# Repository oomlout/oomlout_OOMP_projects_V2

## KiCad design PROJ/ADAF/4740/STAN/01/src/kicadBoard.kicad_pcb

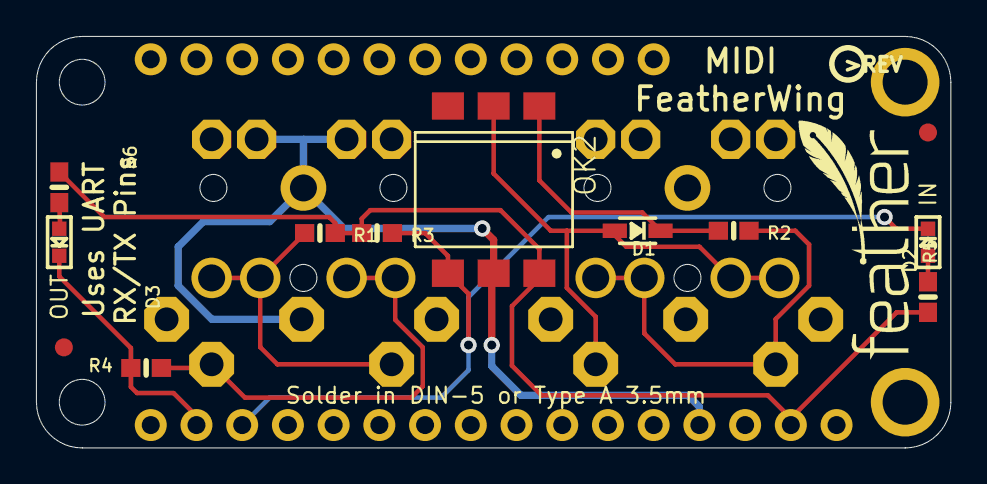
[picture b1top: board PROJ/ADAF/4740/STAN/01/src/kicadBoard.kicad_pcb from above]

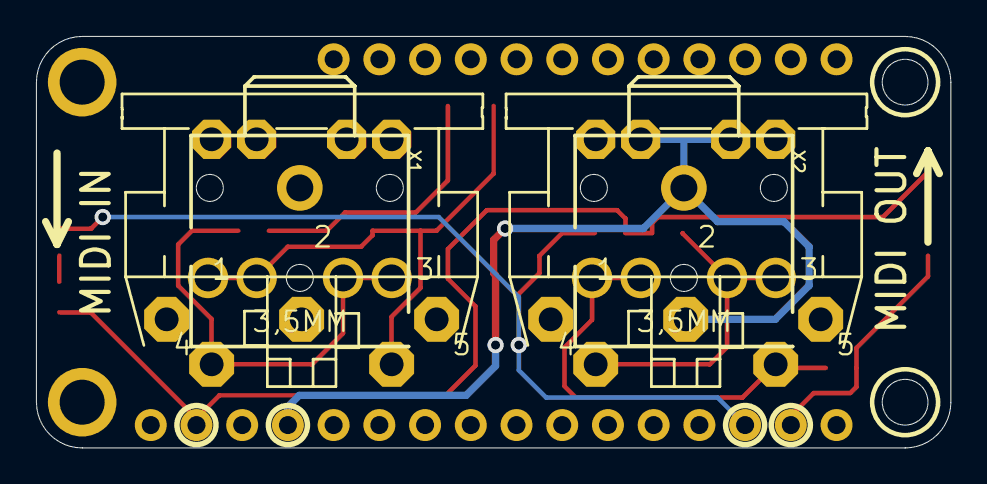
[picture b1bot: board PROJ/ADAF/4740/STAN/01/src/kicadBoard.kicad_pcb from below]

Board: 2 copper layers, 50.8 x 22.9 mm, 19 parts (5 on the bottom side), 11 nets.

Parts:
D1: 1N4148; SOD-323
D2, D3: BLUE; CHIPLED_0603
FID1, FID2: FIDUCIAL_1MM
MIDIIN0: DIN_5; CP-2350
MIDIOUT0: DIN_5; CP-2350
MS1: FEATHERWING_NODIM
OK2: H11L1MS; DIL6-SMD
R1: 33; 0603-NO
R2: 220; 0603-NO
R3: 470; 0603-NO
R4: 10; 0603-NO
R5, R6: 2.2K; 0603-NO
U$8: PCBFEAT-REV-040
U$9: FEATHERLOGO_SMALL
X1, X2: 3.5mm; STX3100

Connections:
3.3V: MS1.2, OK2.6, R1.2, R3.1, R5.1, R6.1
GND: MIDIOUT0.2, MIDIOUT0.PE, MIDIOUT0.PE@, MS1.4, OK2.5, X2.1
IN_SINK: D1.A, MIDIIN0.5, OK2.2, X1.4, X1.5
IN_SOURCE: MIDIIN0.4, R2.2, X1.2, X1.3
MIDI_RX: D2.C, MS1.14, OK2.4, R3.2
MIDI_TX: D3.C, MS1.15, R4.2
unnamed: D2.A, R5.2
unnamed: D3.A, R6.2
unnamed: D1.C, OK2.1, R2.1
OUT_SINK: MIDIOUT0.5, R4.1, X2.4, X2.5
OUT_SOURCE: MIDIOUT0.4, R1.1, X2.2, X2.3

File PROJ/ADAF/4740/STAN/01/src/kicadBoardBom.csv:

"Id";"Designator";"Package";"Quantity";"Designation";"Supplier and ref";
1;"U$8";"PCBFEAT-REV-040";1;"";;;
2;"R6,R5";"0603-NO";2;"2.2K";;;
3;"D1";"SOD-323";1;"1N4148";;;
4;"R2";"0603-NO";1;"220";;;
5;"D2,D3";"CHIPLED_0603";2;"BLUE";;;
6;"FID1,FID2";"FIDUCIAL_1MM";2;"FIDUCIAL_1MM";;;
7;"R4";"0603-NO";1;"10";;;
8;"R3";"0603-NO";1;"470";;;
9;"U$9";"FEATHERLOGO_SMALL";1;"";;;
10;"OK2";"DIL6-SMD";1;"H11L1MS";;;
11;"R1";"0603-NO";1;"33";;;
12;"MS1";"FEATHERWING_NODIM";1;"FEATHERWING_NODIM";;;
13;"X1,X2";"STX3100";2;"3.5mm";;;
14;"MIDIOUT0,MIDIIN0";"CP-2350";2;"DIN_5";;;

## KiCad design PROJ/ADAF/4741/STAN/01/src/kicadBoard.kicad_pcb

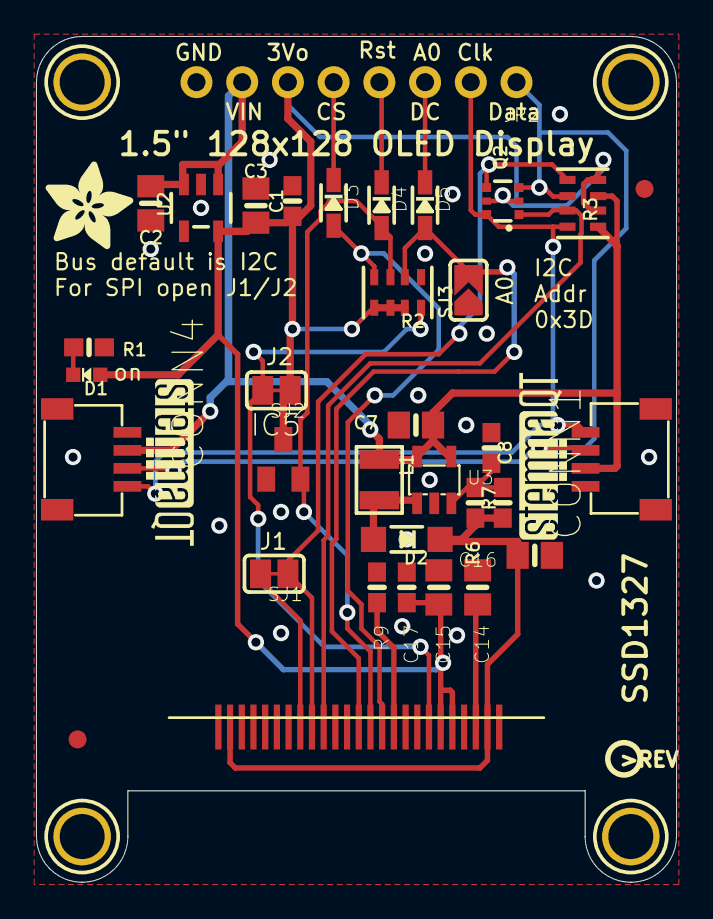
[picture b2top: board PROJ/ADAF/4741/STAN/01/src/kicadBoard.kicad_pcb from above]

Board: 2 copper layers, 35.6 x 47.0 mm, 42 parts (1 on the bottom side), 21 nets.

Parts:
C1, C8: 0.1uF; 0603-NO
C2, C3, C7, C14, C15, C16: 10uF; 0805-NO
C17: 1uF; 0603-NO
CONN1, CONN4: STEMMA_I2C_QT; JST_SH4
D1: GREEN; CHIPLED_0603_NOOUTLINE
D2: MBR120; SOD-123
D3, D4, D5: 1N4148; SOD-323
FID3, FID4: FIDUCIAL_1MM
IC5: APX803; SOT23
JP2: 1X08_ROUND_70
L1: 10uH; INDUCTOR_1007
Q2: BSS138; SOT363
R1, R7: 10K; 0603-NO
R2, R3: 10K; RESPACK_4X0603
R6: 100K; 0603-NO
R9: 390K; 0603-NO
SJ1, SJ2: SOLDERJUMPER_CLOSEDWIRE
SJ3: SOLDERJUMPER_ARROW_NOPASTE
U2: AP2112K-3.3; SOT23-5
U3: FAN5331SX; SOT23-5@1
U$1, U$17, U$19, U$21: MOUNTINGHOLE2.5; MOUNTINGHOLE_2.5_PLATED
U$8: ADAFRUIT_5MM
U$20, U$31: STEMMAQT
U$25: PCBFEAT-REV-040
X1: OLED_1.5_128X128_MONO; OLED_1.5IN_128X128MONO

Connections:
3.3V: C1.1, C3.1, C15.2, C17.2, D1.A, IC5.3, JP2.6, Q2.2, Q2.5, R2.5, R2.6, R2.7, R3.2, R3.4, SJ2.1, U2.5, X1.5, X1.6
12V: C8.1, C16.2, D2.C, R6.2, X1.2, X1.24
CS_3.3V: D3.A, R2.4, X1.11
CS_5.0V: D3.C, JP2.5
D0/SCLK/SCK_3.3V: Q2.1, R3.7, X1.16
D1/MOSI/SDA1_3.3V: Q2.4, R3.5, SJ1.1, X1.17
DC/SA0_3.3V: D5.A, R2.2, SJ3.2, X1.13
DC/SA0_5.0V: D5.C, JP2.3
GND: C1.2, C2.2, C3.2, C7.2, C14.1, C15.1, C16.1, C17.1, CONN1.1, CONN4.1, IC5.1, JP2.8, R1.2, R2.1, R7.1, R9.1, SJ3.1, U2.2, U3.2, X1.1, X1.4, X1.8, X1.9, X1.14, X1.15, X1.19, X1.20, X1.21, X1.22, X1.23, X1.25
unnamed: D1.C, R1.1
unnamed: D2.A, L1.P$2, U3.1
unnamed: C8.2, R6.1, R7.2, U3.3
unnamed: R2.8, SJ2.2, X1.7
unnamed: R9.2, X1.10
unnamed: C14.2, X1.3
unnamed: SJ1.2, X1.18
RST_3.3V: D4.A, IC5.2, R2.3, X1.12
RST_5.0V: D4.C, JP2.4
SCL: CONN1.4, CONN4.4, JP2.2, Q2.6, R3.8
SDA: CONN1.3, CONN4.3, JP2.1, Q2.3, R3.6
VCC: C2.1, C7.1, CONN1.2, CONN4.2, JP2.7, L1.P$1, R3.1, R3.3, U2.1, U2.3, U3.4, U3.5

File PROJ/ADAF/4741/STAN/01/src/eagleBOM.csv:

"Part";"Value";"Device";"Package";"Description";"BOM";
"C1";"0.1uF";"CAP_CERAMIC0603_NO";"0603-NO";"Ceramic Capacitors";"";
"C2";"10uF";"CAP_CERAMIC0805-NOOUTLINE";"0805-NO";"Ceramic Capacitors";"";
"C3";"10uF";"CAP_CERAMIC0805-NOOUTLINE";"0805-NO";"Ceramic Capacitors";"";
"C7";"10uF";"CAP_CERAMIC0805-NOOUTLINE";"0805-NO";"Ceramic Capacitors";"";
"C8";"0.1uF";"CAP_CERAMIC0603_NO";"0603-NO";"Ceramic Capacitors";"";
"C14";"10uF";"CAP_CERAMIC0805-NOOUTLINE";"0805-NO";"Ceramic Capacitors";"";
"C15";"10uF";"CAP_CERAMIC0805-NOOUTLINE";"0805-NO";"Ceramic Capacitors";"";
"C16";"10uF";"CAP_CERAMIC0805-NOOUTLINE";"0805-NO";"Ceramic Capacitors";"";
"C17";"1uF";"CAP_CERAMIC0603_NO";"0603-NO";"Ceramic Capacitors";"";
"CONN1";"STEMMA_I2C_QT";"STEMMA_I2C_QT";"JST_SH4";"";"";
"CONN4";"STEMMA_I2C_QT";"STEMMA_I2C_QT";"JST_SH4";"";"";
"D1";"GREEN";"LED0603_NOOUTLINE";"CHIPLED_0603_NOOUTLINE";"LED";"";
"D2";"MBR120";"DIODESOD-123";"SOD-123";"Diode";"";
"D3";"1N4148";"DIODESOD-323";"SOD-323";"Diode";"";
"D4";"1N4148";"DIODESOD-323";"SOD-323";"Diode";"";
"D5";"1N4148";"DIODESOD-323";"SOD-323";"Diode";"";
"FID3";"FIDUCIAL_1MM";"FIDUCIAL_1MM";"FIDUCIAL_1MM";"Fiducial Alignment Points";"EXCLUDE";
"FID4";"FIDUCIAL_1MM";"FIDUCIAL_1MM";"FIDUCIAL_1MM";"Fiducial Alignment Points";"EXCLUDE";
"IC5";"APX803";"AXP083-SAG";"SOT23";"";"";
"JP2";"";"HEADER-1X870MIL";"1X08_ROUND_70";"PIN HEADER";"";
"L1";"10uH";"INDUCTOR";"INDUCTOR_1007";"Inductors";"";
"Q2";"BSS138";"MOSFET-N_DUAL";"SOT363";"Dual N-Channel MOSFET";"";
"R1";"10K";"RESISTOR_0603_NOOUT";"0603-NO";"Resistors";"";
"R2";"10K";"RESISTOR_4PACK";"RESPACK_4X0603";"Resistor Packs (4 resistors)";"";
"R3";"10K";"RESISTOR_4PACK";"RESPACK_4X0603";"Resistor Packs (4 resistors)";"";
"R6";"100K";"RESISTOR_0603_NOOUT";"0603-NO";"Resistors";"";
"R7";"10K";"RESISTOR_0603_NOOUT";"0603-NO";"Resistors";"";
"R9";"390K";"RESISTOR_0603_NOOUT";"0603-NO";"Resistors";"";
"SJ1";"";"SOLDERJUMPERCLOSED";"SOLDERJUMPER_CLOSEDWIRE";"SMD Solder JUMPER";"";
"SJ2";"";"SOLDERJUMPERCLOSED";"SOLDERJUMPER_CLOSEDWIRE";"SMD Solder JUMPER";"";
"SJ3";"";"SOLDERJUMPER";"SOLDERJUMPER_ARROW_NOPASTE";"SMD Solder JUMPER";"EXCLUDE";
"U$1";"MOUNTINGHOLE2.5";"MOUNTINGHOLE2.5";"MOUNTINGHOLE_2.5_PLATED";"Mounting Hole";"EXCLUDE";
"U$17";"MOUNTINGHOLE2.5";"MOUNTINGHOLE2.5";"MOUNTINGHOLE_2.5_PLATED";"Mounting Hole";"EXCLUDE";
"U$19";"MOUNTINGHOLE2.5";"MOUNTINGHOLE2.5";"MOUNTINGHOLE_2.5_PLATED";"Mounting Hole";"EXCLUDE";
"U$21";"MOUNTINGHOLE2.5";"MOUNTINGHOLE2.5";"MOUNTINGHOLE_2.5_PLATED";"Mounting Hole";"EXCLUDE";
"U2";"AP2112K-3.3";"VREG_SOT23-5";"SOT23-5";"SOT23-5 Fixed Voltage Regulators";"";
"U3";"FAN5331SX";"FAN5331";"SOT23-5@1";"FAN5331 - LED/OLED 20V Boost Converter";"";
"X1";"OLED_1.5_128X128_MONO";"OLED_1.5_128X128_MONO";"OLED_1.5IN_128X128MONO";"";"";

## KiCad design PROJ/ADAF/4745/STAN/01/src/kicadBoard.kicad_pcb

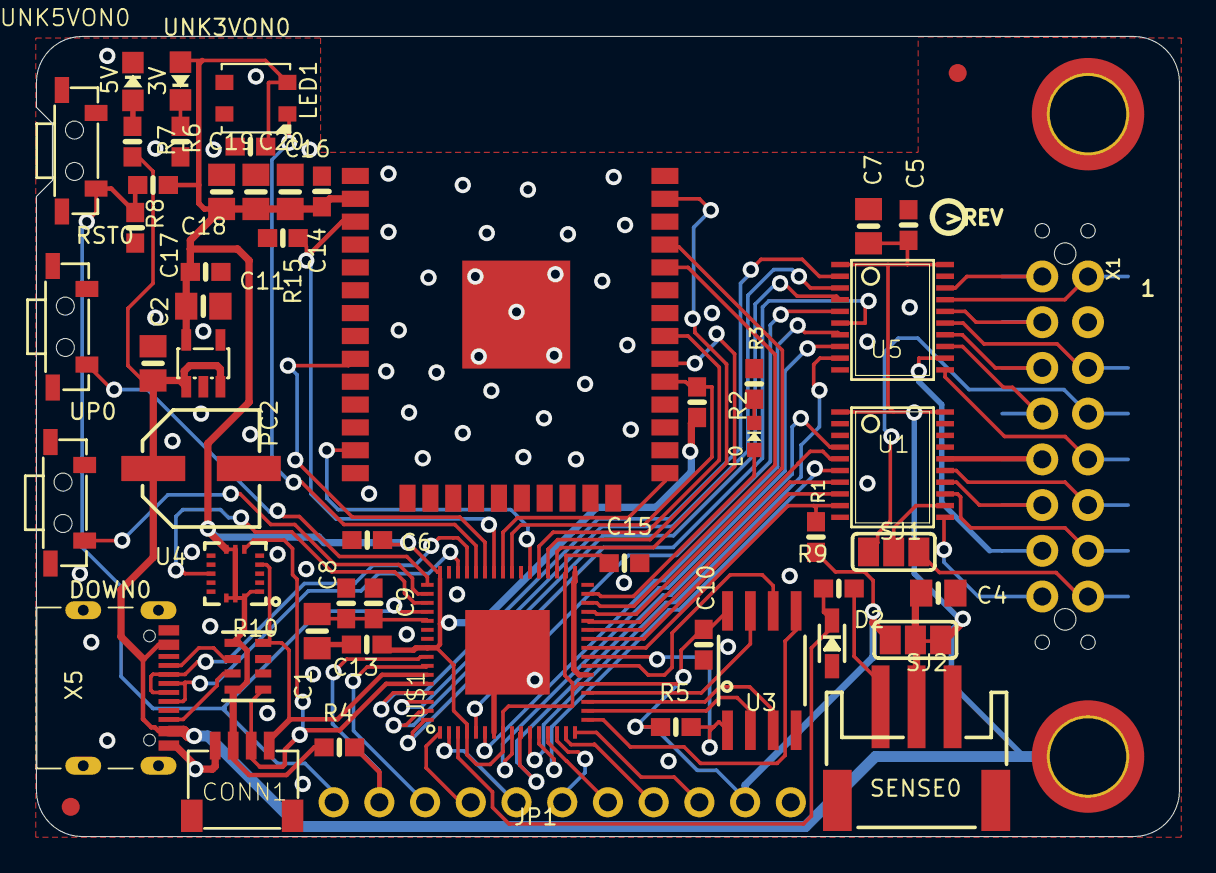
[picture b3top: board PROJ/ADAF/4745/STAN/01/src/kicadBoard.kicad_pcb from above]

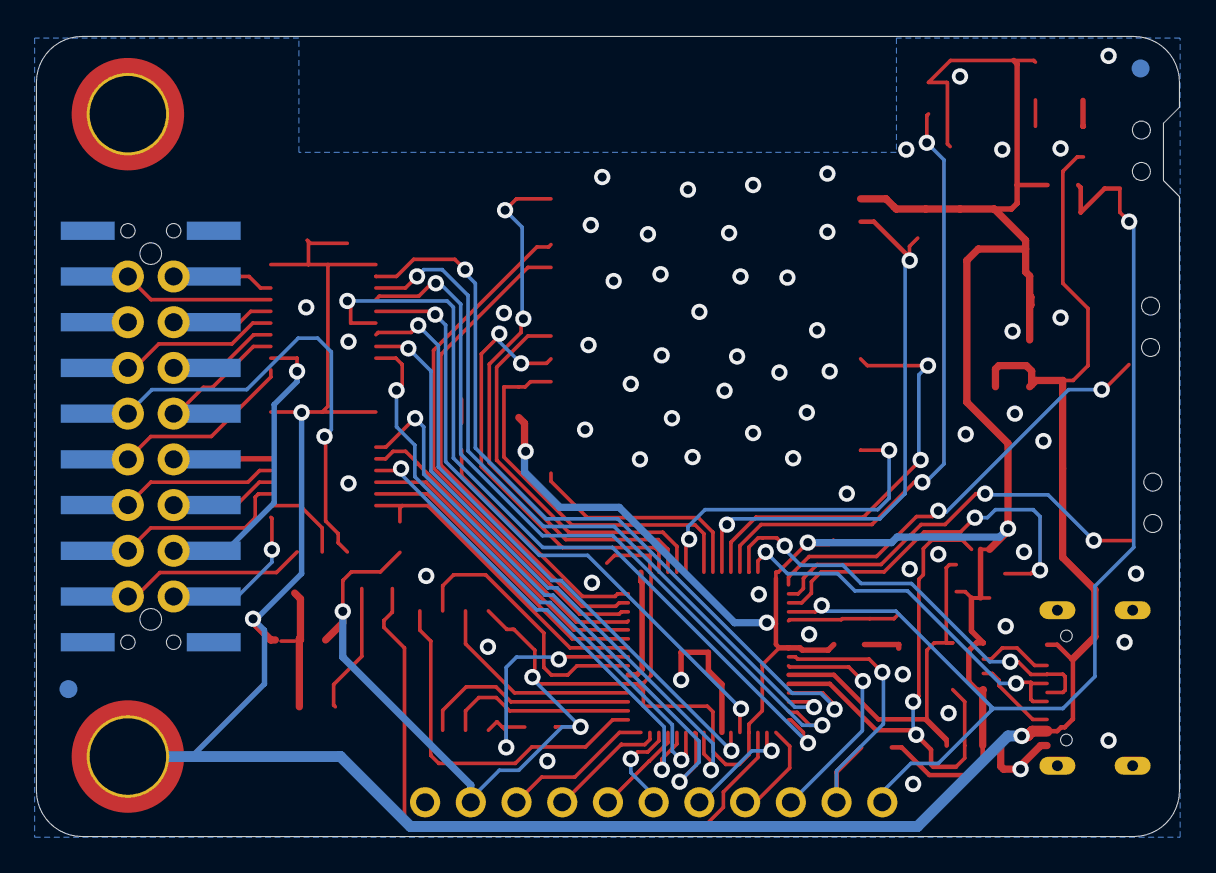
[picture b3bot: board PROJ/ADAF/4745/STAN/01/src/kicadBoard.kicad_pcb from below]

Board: 2 copper layers, 63.5 x 44.5 mm, 62 parts (3 on the bottom side), 76 nets.

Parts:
C1, C2, C3, C4, C7, C18, C19, C20: 10uF; 0805-NO
C5, C13, C17: 0.1uF; 0603-NO
C6, C8, C10, C11, C14, C15, C16: .1u; 0603-NO
C9: 1uF; 0603-NO
CONN1: STEMMA_I2C_QT; JST_SH4
D2: 3.6V; SOD-323
DOWN0: TL3330AF260QG; SPST_TACTILE_RA
FID1, FID2, FID3, FID4: FIDUCIAL_1MM
JP1: 1X11_ROUND
L0: RED; CHIPLED_0603_NOOUTLINE
LED1: WS2812B3535; LED3535
PC2: 47uF+/6.3V+; PANASONIC_D
R1, R2, R5, R6, R7, R15: 10K; 0603-NO
R3, R8: 5.1K; 0603-NO
R4, R9: 1K; 0603-NO
R10: 5.1K; RESPACK_4X0603
RST0: TL3330AF260QG; SPST_TACTILE_RA
SENSE0: JST PH 3; JSTPH3
SJ1, SJ2: SOLDERJUMPER_2WAY_OPEN_NOPASTE
TP1, TP2: SEWTAP_SMTNUTM3; SMT_NUT_3MM
U1, U5: 74AHCT245; TSSOP20
U2: AP2112K-3.3; SOT23-DBV
U3: GD25Q16; SOIC8_208MIL
U4: LIS3DHTR; LGA16_3X3MM
U$1: ATSAMD51J19; PQFN64-1
U$41: MATRIXPORTAL_BOT
U$44: PCBFEAT-REV-040
U$45: MATRIXPORTAL_TOP
UNK3VON0, UNK5VON0: GREEN; CHIPLED_0805_NOOUTLINE
UP0: TL3330AF260QG; SPST_TACTILE_RA
X1: RGBMATRIX_THMSMT; 2X08_SMTTHM_RGBMATRIX
X5: USB TYPE C; USB_C_CUSB31-CFM2AX-01-X
X6: ESP32_WROOM32; WROOM32

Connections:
3.3V: C3.2, C6.2, C10.2, C11.2, C13.1, C14.2, C15.2, C16.2, C18.1, C19.1, C20.1, CONN1.2, JP1.2, LED1.2, R1.1, R2.1, R4.2, R5.2, R8.2, R10.1, R10.4, SJ2.3, U2.5, U3.8, U4.1, U4.7, U4.8, U4.14, U4.15, U4.16, U$1.4, U$1.8, U$1.21, U$1.34, U$1.48, U$1.56, UNK3VON0.A, X6.2
+5V: C2.2, C5.2, C7.2, PC2.+, R7.1, SJ2.1, TP1.P$1, U1.1, U1.20, U2.1, U2.3, U5.1, U5.20, X5.A4B9, X5.B4A9
A0: D2.C, R9.2, U$1.3
A0_JST: R9.1, SENSE0.3
A1: JP1.6, U$1.14
A2: JP1.5, U$1.13
A3: JP1.4, U$1.15
A4: JP1.3, U$1.16
ADDRA_3V: U1.4, U$1.10
ADDRB_3V: U5.9, U$1.11
ADDRC_3V: U1.6, U$1.12
ADDRD_3V: U1.5, U$1.28
ADDRE_3V: U1.8, U$1.26
B1_3V: U5.4, U$1.63
B2_3V: U5.7, U$1.6
CC1: R10.2, X5.A5
CC2: R10.3, X5.B5
CLK: U5.12, X1.13, X1.13S
CLK_3V: U5.8, U$1.9
D+: U$1.46, X5.A6, X5.B6
D-: U$1.45, X5.A7, X5.B7
DOWN: DOWN0.2, U$1.50
ESP_BUSY: U$1.43, X6.9
ESP_CS: R2.2, U$1.40, X6.29
ESP_GPIO0: U$1.41, X6.25
ESP_RESET: R15.1, U$1.42, X6.3
ESP_RTS: U$1.37, X6.31
ESP_RXD: U$1.29, X6.35
ESP_TXD: U$1.30, X6.34
FLASH_CS: R5.1, U3.1, U$1.24
FLASH_IO0: U3.5, U$1.17
FLASH_IO1: U3.2, U$1.18
FLASH_IO2: U3.3, U$1.19
FLASH_IO3: U3.7, U$1.20
FLASH_SCK: U3.6, U$1.23
G1_3V: U5.3, U$1.62
G2_3V: U5.5, U$1.5
GND: C1.2, C2.1, C3.1, C4.2, C5.1, C6.1, C7.1, C8.1, C9.2, C10.1, C11.1, C13.2, C14.1, C15.1, C16.1, C17.1, C18.2, C19.2, C20.2, CONN1.1, D2.A, DOWN0.1, DOWN0.MT1, DOWN0.MT2, JP1.1, LED1.4, PC2.-, R3.2, R6.2, R10.6, R10.7, R15.2, RST0.1, RST0.MT1, RST0.MT2, SENSE0.1, TP2.P$1, U1.2, U1.3, U1.10, U1.19, U2.2, U3.4, U4.5, U4.10, U4.12, U4.13, U5.10, U5.19, U$1.7, U$1.22, U$1.33, U$1.47, U$1.54, U$1.EXP, UNK5VON0.C, UP0.1, UP0.MT1, UP0.MT2, X1.4, X1.4S, X5.A1B12, X5.B1A12, X6.1, X6.15, X6.38, X6.P$1
INT: U4.11, U$1.51
LAT: U1.13, X1.14, X1.14S
LAT_3V: U1.7, U$1.27
M1_A: U1.16, X1.9, X1.9S
M1_B: U5.11, X1.10, X1.10S
M1_B1: U5.16, X1.3, X1.3S
M1_B2: U5.13, X1.7, X1.7S
M1_C: U1.14, X1.11, X1.11S
M1_D: U1.15, X1.12, X1.12S
M1_E: SJ1.2, U1.12
M1_E8: SJ1.1, X1.8, X1.8S
M1_E16: SJ1.3, X1.16, X1.16S
M1_G1: U5.17, X1.2, X1.2S
M1_G2: U5.15, X1.6, X1.6S
M1_R1: U5.18, X1.1, X1.1S
M1_R2: U5.14, X1.5, X1.5S
MISO: U$1.36, X6.37
MOSI: U$1.38, X6.13
unnamed: R7.2, UNK5VON0.A
unnamed: R6.1, UNK3VON0.C
unnamed: L0.A, U$1.31
unnamed: L0.C, R3.1
NEOPIX: LED1.1, U$1.44
OE: U1.11, X1.15, X1.15S
OE_3V: R1.2, U1.9, U$1.25
R1_3V: U5.2, U$1.61
R2_3V: U5.6, U$1.64
RXI: JP1.7, U$1.2
SCK: U$1.35, X6.30
SCL: CONN1.4, R10.8, U4.4, U$1.59
SDA: CONN1.3, R10.5, U4.6, U$1.60
SWCLK: JP1.10, R4.1, U$1.57
SWDIO: JP1.9, U$1.58
TXO: JP1.8, U$1.1
UP: U$1.49, UP0.2
VCC: C4.1, SENSE0.2, SJ2.2
VDDCORE: C1.1, C8.2, C9.1, U$1.53
~RESET: C17.2, JP1.11, R8.1, RST0.2, U$1.52

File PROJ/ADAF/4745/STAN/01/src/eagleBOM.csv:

"Part";"Value";"Device";"Package";"Description";"BOM";
"3VON";"GREEN";"LED0805_NOOUTLINE";"CHIPLED_0805_NOOUTLINE";"LED";"";
"5VON";"GREEN";"LED0805_NOOUTLINE";"CHIPLED_0805_NOOUTLINE";"LED";"";
"C1";"10uF";"CAP_CERAMIC0805-NOOUTLINE";"0805-NO";"Ceramic Capacitors";"";
"C2";"10uF";"CAP_CERAMIC0805-NOOUTLINE";"0805-NO";"Ceramic Capacitors";"";
"C3";"10uF";"CAP_CERAMIC0805-NOOUTLINE";"0805-NO";"Ceramic Capacitors";"";
"C4";"10uF";"CAP_CERAMIC0805-NOOUTLINE";"0805-NO";"Ceramic Capacitors";"";
"C5";"0.1uF";"CAP_CERAMIC0603_NO";"0603-NO";"Ceramic Capacitors";"";
"C6";".1u";"CAP_CERAMIC0603_NO";"0603-NO";"Ceramic Capacitors";"";
"C7";"10uF";"CAP_CERAMIC0805-NOOUTLINE";"0805-NO";"Ceramic Capacitors";"";
"C8";".1u";"CAP_CERAMIC0603_NO";"0603-NO";"Ceramic Capacitors";"";
"C9";"1uF";"CAP_CERAMIC0603_NO";"0603-NO";"Ceramic Capacitors";"";
"C10";".1u";"CAP_CERAMIC0603_NO";"0603-NO";"Ceramic Capacitors";"";
"C11";".1u";"CAP_CERAMIC0603_NO";"0603-NO";"Ceramic Capacitors";"";
"C13";"0.1uF";"CAP_CERAMIC0603_NO";"0603-NO";"Ceramic Capacitors";"";
"C14";".1u";"CAP_CERAMIC0603_NO";"0603-NO";"Ceramic Capacitors";"";
"C15";".1u";"CAP_CERAMIC0603_NO";"0603-NO";"Ceramic Capacitors";"";
"C16";".1u";"CAP_CERAMIC0603_NO";"0603-NO";"Ceramic Capacitors";"";
"C17";"0.1uF";"CAP_CERAMIC0603_NO";"0603-NO";"Ceramic Capacitors";"";
"C18";"10uF";"CAP_CERAMIC0805-NOOUTLINE";"0805-NO";"Ceramic Capacitors";"";
"C19";"10uF";"CAP_CERAMIC0805-NOOUTLINE";"0805-NO";"Ceramic Capacitors";"";
"C20";"10uF";"CAP_CERAMIC0805-NOOUTLINE";"0805-NO";"Ceramic Capacitors";"";
"CONN1";"STEMMA_I2C_QT";"STEMMA_I2C_QT";"JST_SH4";"";"";
"D2";"3.6V";"DIODE-ZENERSOD323";"SOD-323";"Zener Diode";"";
"DOWN";"TL3330AF260QG";"SWITCH_SPST_TACT_RA";"SPST_TACTILE_RA";"Switch - SPST";"";
"FID1";"FIDUCIAL_1MM";"FIDUCIAL_1MM";"FIDUCIAL_1MM";"Fiducial Alignment Points";"EXCLUDE";
"FID2";"FIDUCIAL_1MM";"FIDUCIAL_1MM";"FIDUCIAL_1MM";"Fiducial Alignment Points";"EXCLUDE";
"FID3";"FIDUCIAL_1MM";"FIDUCIAL_1MM";"FIDUCIAL_1MM";"Fiducial Alignment Points";"EXCLUDE";
"FID4";"FIDUCIAL_1MM";"FIDUCIAL_1MM";"FIDUCIAL_1MM";"Fiducial Alignment Points";"EXCLUDE";
"JP1";"";"HEADER-1X11";"1X11_ROUND";"";"";
"L";"RED";"LED0603_NOOUTLINE";"CHIPLED_0603_NOOUTLINE";"LED";"";
"LED1";"WS2812B3535";"WS2812B3535";"LED3535";"";"";
"PC2";"47uF+/6.3V+";"CAP_ELECTROLYTICPANASONIC_D";"PANASONIC_D";"Electrolytic Capacitors";"";
"R1";"10K";"RESISTOR_0603_NOOUT";"0603-NO";"Resistors";"";
"R2";"10K";"RESISTOR_0603_NOOUT";"0603-NO";"Resistors";"";
"R3";"5.1K";"RESISTOR_0603_NOOUT";"0603-NO";"Resistors";"";
"R4";"1K";"RESISTOR_0603_NOOUT";"0603-NO";"Resistors";"";
"R5";"10K";"RESISTOR_0603_NOOUT";"0603-NO";"Resistors";"";
"R6";"10K";"RESISTOR_0603_NOOUT";"0603-NO";"Resistors";"";
"R7";"10K";"RESISTOR_0603_NOOUT";"0603-NO";"Resistors";"";
"R8";"5.1K";"RESISTOR_0603_NOOUT";"0603-NO";"Resistors";"";
"R9";"1K";"RESISTOR_0603_NOOUT";"0603-NO";"Resistors";"";
"R10";"5.1K";"RESISTOR_4PACK";"RESPACK_4X0603";"Resistor Packs (4 resistors)";"";
"R15";"10K";"RESISTOR_0603_NOOUT";"0603-NO";"Resistors";"";
"RST";"TL3330AF260QG";"SWITCH_SPST_TACT_RA";"SPST_TACTILE_RA";"Switch - SPST";"";
"SENSE";"JST PH 3";"CON_JST_PH_3PIN";"JSTPH3";"";"";
"SJ1";"";"SOLDERJUMPER_2WAY";"SOLDERJUMPER_2WAY_OPEN_NOPASTE";"2-Way Solder Jumper";"";
"SJ2";"";"SOLDERJUMPER_2WAY";"SOLDERJUMPER_2WAY_OPEN_NOPASTE";"2-Way Solder Jumper";"";
"TP1";"SEWTAP_SMTNUTM3";"SEWTAP_SMTNUTM3";"SMT_NUT_3MM";"";"";
"TP2";"SEWTAP_SMTNUTM3";"SEWTAP_SMTNUTM3";"SMT_NUT_3MM";"";"";
"U$1";"ATSAMD51J19";"ATSAMD51J";"PQFN64-1";"ATSAMD51J cortex m4 microcontroller";"";
"U1";"74AHCT245";"74LCX245";"TSSOP20";"74LCX245MTC - 5.0V Tolerant Bi-Directional Buffer";"";
"U2";"AP2112K-3.3";"LP2985-XXDBVR33";"SOT23-DBV";"ULTRALOW-POWER 50-mA LOW-DROPOUT LINEAR REGULATORS";"";
"U3";"GD25Q16";"SPIFLASH_8PIN208MIL";"SOIC8_208MIL";"SOIC8 SPI Flash";"";
"U4";"LIS3DHTR";"ACCEL_LIS3DHTR";"LGA16_3X3MM";"LIS3DHTR 3-Axis Accelerometer with I2C/SPI Interface";"";
"U5";"74AHCT245";"74LCX245";"TSSOP20";"74LCX245MTC - 5.0V Tolerant Bi-Directional Buffer";"";
"UP";"TL3330AF260QG";"SWITCH_SPST_TACT_RA";"SPST_TACTILE_RA";"Switch - SPST";"";
"X1";"RGBMATRIX_THMSMT";"RGBMATRIX_THMSMT";"2X08_SMTTHM_RGBMATRIX";"";"";
"X5";"USB TYPE C";"USB_C";"USB_C_CUSB31-CFM2AX-01-X";"USB Type-C USB 2.0 Connector";"";
"X6";"ESP32_WROOM32";"ESP32_WROOM32";"WROOM32";"";"";

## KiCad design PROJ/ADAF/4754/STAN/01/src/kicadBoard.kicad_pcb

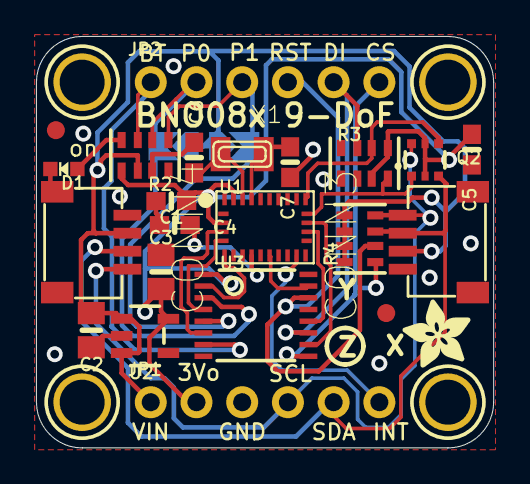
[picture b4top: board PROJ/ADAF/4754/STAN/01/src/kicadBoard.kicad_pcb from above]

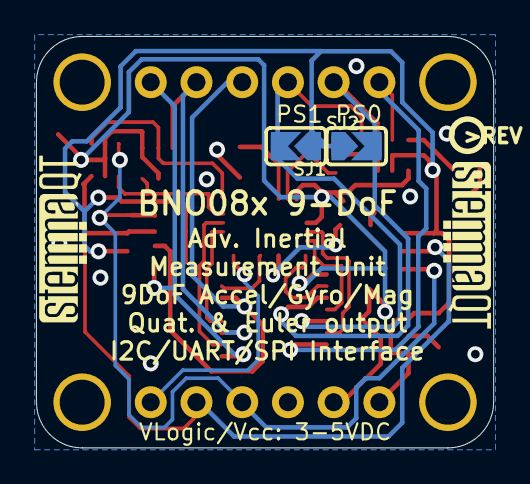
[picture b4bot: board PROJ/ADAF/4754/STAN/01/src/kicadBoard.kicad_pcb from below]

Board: 2 copper layers, 25.4 x 22.9 mm, 32 parts (5 on the bottom side), 24 nets.

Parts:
C1, C4, C5: 0.1uF; 0603-NO
C2, C3: 10uF; 0805-NO
C6, C7: 22pF; 0603-NO
CONN3, CONN4: STEMMA_I2C_QT; JST_SH4
D1: GREEN; CHIPLED_0603_NOOUTLINE
FID3, FID4: FIDUCIAL_1MM
JP1, JP2: 1X06_ROUND_70
Q2: BSS138; SOT363
R2, R3, R4: 10K; RESPACK_4X0603
SJ1: PS1; SOLDERJUMPER_ARROW_NOPASTE
SJ2: PS0; SOLDERJUMPER_ARROW_NOPASTE
U1: BNO080
U2: AP2112K-3.3; SOT23-5
U3: 74AHC4050; TSSOP16
U$1, U$17, U$19, U$21: MOUNTINGHOLE2.5; MOUNTINGHOLE_2.5_PLATED
U$22: ADAFRUIT_3.5MM
U$25: PCBFEAT-REV-040
U$30, U$31: STEMMAQT
X1: 32.768; XTAL3215

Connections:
3.3V: C1.1, C3.1, C5.1, JP1.2, Q2.2, Q2.5, R2.5, R3.3, R3.5, U1.3, U1.28, U2.5, U3.1
BOOT: JP2.1, R2.3, U3.7
BOOT_3V: U1.4, U3.6
CAP: C4.2, U1.9
CS: JP2.6, R4.1, U3.9
CS_3V: U1.18, U3.10
GND: C1.2, C2.2, C3.2, C4.1, C5.2, C6.2, C7.2, CONN3.1, CONN3.MT1, CONN3.MT2, CONN4.1, CONN4.MT1, CONN4.MT2, D1.C, JP1.3, R2.7, R2.8, R3.1, R3.2, R3.8, U1.2, U1.10, U1.25, U2.2, U3.8
INT: JP1.6, U1.14
MOSI: JP2.5, R3.7, U3.11
MOSI_3V: U1.17, U3.12
unnamed: D1.A, R2.4
PS0: JP2.2, R2.2, SJ2.2, U3.3
PS0_3V: U1.6, U3.2
PS1: JP2.3, R2.1, SJ1.2, U3.5
PS1_3V: U1.5, U3.4
RST: JP2.4, R4.2, U3.14
RST_3V: U1.11, U3.15
SCL/SCK/RX: CONN3.4, CONN4.4, JP1.4, Q2.6, R4.4
SCL_3V: Q2.1, R3.4, U1.19
SDA/MISO/TX: CONN3.3, CONN4.3, JP1.5, Q2.3, R4.3
SDA_3V: Q2.4, R3.6, U1.20
VCC: C2.1, CONN3.2, CONN4.2, JP1.1, R2.6, R4.5, R4.6, R4.7, R4.8, SJ1.1, SJ2.1, U2.1, U2.3
XIN: C6.1, U1.27, X1.P$1
XOUT: C7.1, U1.26, X1.P$2

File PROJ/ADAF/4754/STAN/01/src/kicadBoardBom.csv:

"Id";"Designator";"Package";"Quantity";"Designation";"Supplier and ref";
1;"U3";"TSSOP16";1;"74AHC4050";;;
2;"Q2";"SOT363";1;"BSS138";;;
3;"R4,R2,R3";"RESPACK_4X0603";3;"10K";;;
4;"U2";"SOT23-5";1;"AP2112K-3.3";;;
5;"JP2,JP1";"1X06_ROUND_70";2;"";;;
6;"C3,C2";"0805-NO";2;"10uF";;;
7;"FID4,FID3";"FIDUCIAL_1MM";2;"FIDUCIAL_1MM";;;
8;"C5,C1,C4";"0603-NO";3;"0.1uF";;;
9;"C6,C7";"0603-NO";2;"22pF";;;
10;"U$22";"ADAFRUIT_3.5MM";1;"";;;
11;"U$19,U$1,U$17,U$21";"MOUNTINGHOLE_2.5_PLATED";4;"MOUNTINGHOLE2.5";;;
12;"CONN3,CONN4";"JST_SH4";2;"STEMMA_I2C_QT";;;
13;"X1";"XTAL3215";1;"32.768";;;
14;"U1";"BNO080";1;"BNO080";;;
15;"D1";"CHIPLED_0603_NOOUTLINE";1;"GREEN";;;
16;"SJ2";"SOLDERJUMPER_ARROW_NOPASTE";1;"PS0";;;
17;"U$25";"PCBFEAT-REV-040";1;"";;;
18;"U$31,U$30";"STEMMAQT";2;"";;;
19;"SJ1";"SOLDERJUMPER_ARROW_NOPASTE";1;"PS1";;;

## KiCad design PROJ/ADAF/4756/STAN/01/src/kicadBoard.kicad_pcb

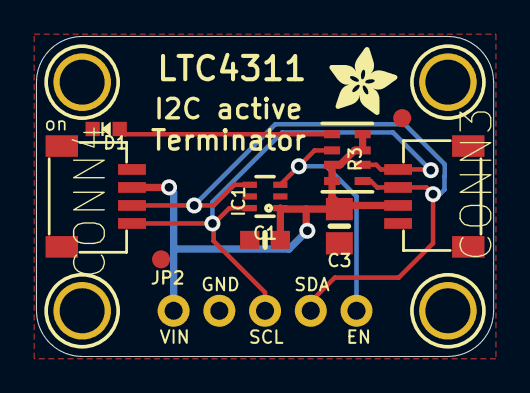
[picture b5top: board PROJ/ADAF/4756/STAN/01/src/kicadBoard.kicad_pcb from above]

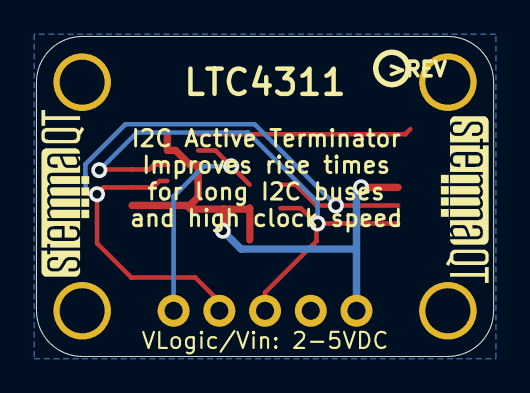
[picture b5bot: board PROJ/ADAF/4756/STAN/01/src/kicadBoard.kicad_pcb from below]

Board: 2 copper layers, 25.4 x 17.8 mm, 18 parts (3 on the bottom side), 6 nets.

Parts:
C1: 0.1uF; 0603-NO
C3: 10uF; 0805-NO
CONN3, CONN4: STEMMA_I2C_QT; JST_SH4
D1: GREEN; CHIPLED_0603_NOOUTLINE
FID3, FID4: FIDUCIAL_1MM
IC1: LTC4311_SC70; SC70-6L
JP2: 1X05_ROUND_70
R3: 10K; RESPACK_4X0603
U$1, U$17, U$19, U$21: MOUNTINGHOLE2.5; MOUNTINGHOLE_2.5_PLATED
U$22: ADAFRUIT_3.5MM
U$25: PCBFEAT-REV-040
U$30, U$31: STEMMAQT

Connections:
EN: IC1.3, JP2.5, R3.6
GND: C1.2, C3.2, CONN3.1, CONN4.1, D1.C, IC1.2, IC1.5, JP2.2
unnamed: D1.A, R3.5
SCL: CONN3.4, CONN4.4, IC1.6, JP2.3, R3.2
SDA: CONN3.3, CONN4.3, IC1.4, JP2.4, R3.1
VCC: C1.1, C3.1, CONN3.2, CONN4.2, IC1.1, JP2.1, R3.3, R3.4, R3.7, R3.8

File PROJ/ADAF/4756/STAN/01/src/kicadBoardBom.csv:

"Id";"Designator";"Package";"Quantity";"Designation";"Supplier and ref";
1;"FID4,FID3";"FIDUCIAL_1MM";2;"FIDUCIAL_1MM";;;
2;"U$17,U$21,U$1,U$19";"MOUNTINGHOLE_2.5_PLATED";4;"MOUNTINGHOLE2.5";;;
3;"U$22";"ADAFRUIT_3.5MM";1;"";;;
4;"C1";"0603-NO";1;"0.1uF";;;
5;"R3";"RESPACK_4X0603";1;"10K";;;
6;"IC1";"SC70-6L";1;"LTC4311_SC70";;;
7;"CONN4,CONN3";"JST_SH4";2;"STEMMA_I2C_QT";;;
8;"D1";"CHIPLED_0603_NOOUTLINE";1;"GREEN";;;
9;"C3";"0805-NO";1;"10uF";;;
10;"JP2";"1X05_ROUND_70";1;"";;;
11;"U$25";"PCBFEAT-REV-040";1;"";;;
12;"U$30,U$31";"STEMMAQT";2;"";;;

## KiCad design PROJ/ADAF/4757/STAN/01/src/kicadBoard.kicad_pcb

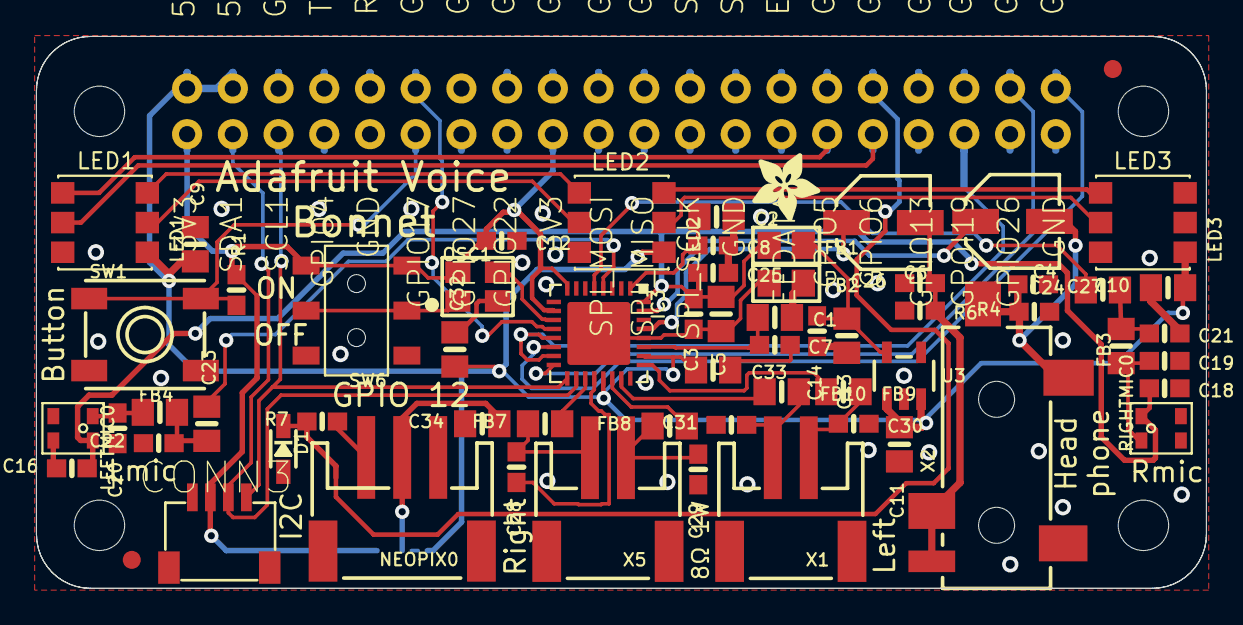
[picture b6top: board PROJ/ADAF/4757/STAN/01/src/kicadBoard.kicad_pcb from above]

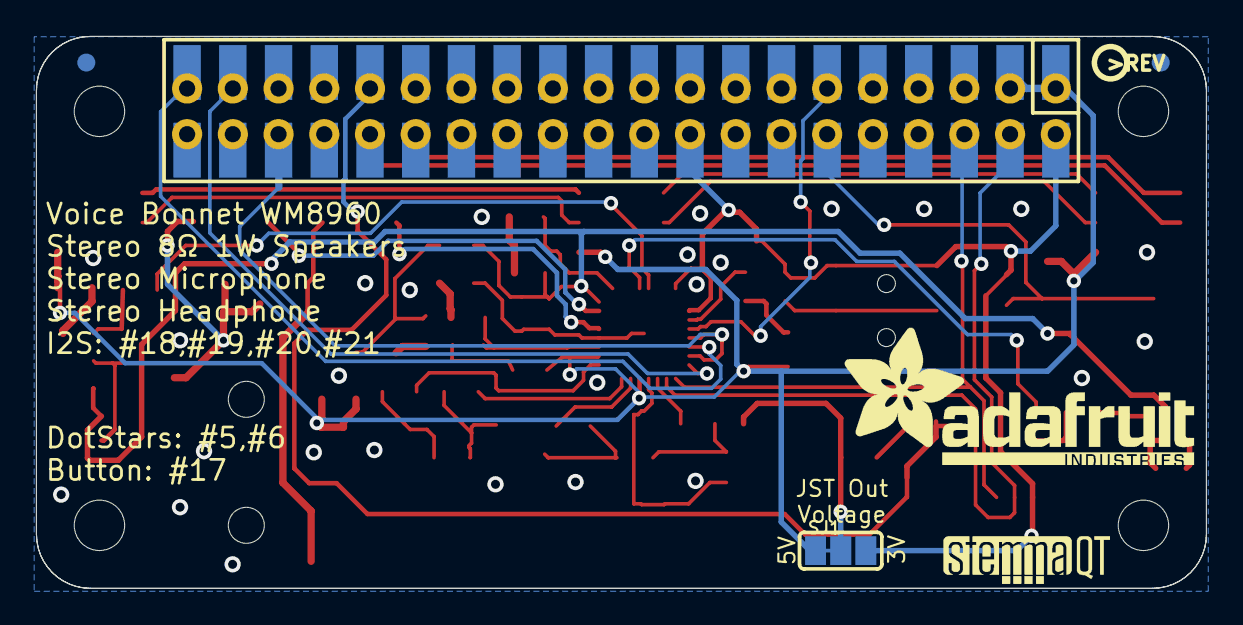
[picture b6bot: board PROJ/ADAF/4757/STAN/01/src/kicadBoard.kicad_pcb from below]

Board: 2 copper layers, 65.0 x 30.7 mm, 69 parts (5 on the bottom side), 62 nets.

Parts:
C1, C2, C5, C9, C10, C11, C13, C23, C24, C32, C34: 10uF; 0805-NO
C3, C7, C8, C12, C14, C16, C18, C25: 0.1uF; 0603-NO
C4, C6: 100uF; PANASONIC_C
C19, C20, C21, C22: 33pF; 0603-NO
C26, C27: 220pF; 0603-NO
C28, C29, C30, C31: 100pF; 0603-NO
C33: 2.2uF+; 0805-NO
CONN3: STEMMA_I2C_QT; JST_SH4
D1: 3.6V; SOD-323
FB1, FB2: Ferrite; 0805
FB3: Ferrite; 0805-NO
FB4: FERRITE; 0805-NO
FB7, FB8, FB9, FB10: 120o; 0805-NO
FID1, FID2: FIDUCIAL_1MM
IC3: WM8960; QFN32_5MM
LED1, LED2, LED3: SK6822; APA102
LEFTMIC0: SPW2430HR5H-B
NEOPIX0: JST PH 3; JSTPH3
OSC1: ECS-3225MV; OSC_3.2X2.5MM
R1, R4: 10K; 0603-NO
R6: 10k; 0603-NO
R7: 1K; 0603-NO
RIGHTMIC0: SPW2430HR5H-B
RPI1: RASPBERRYPI_BPLUS_BONNET_THMSMT; PI_BONNET_THMSMT
SJ1: SOLDERJUMPER_2WAY_OPEN_NOPASTE
SW1: EVQQ; EVQ-Q2_SMALLER
SW6: EG1390
U3: AP2112-3.3K; SOT23-5
U$11: PCBFEAT-REV-040
U$12: STEMMAQT
U$15: ADAFRUIT_3.5MM
U$16: ADAFRUIT_TEXT_20MM
U$79: BRAINPAD_1IN
X1, X5: JSTPH 2P; JSTPH2
X2: 3.5mm; 4UCONN_19269

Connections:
3.3V: C12.1, CONN3.2, IC3.8, IC3.10, OSC1.4, R1.2, RPI1.1, RPI1.17, RPI1.S1, RPI1.S17, SJ1.3, SW6.S1, SW6.S2
5.0V: C9.1, C10.1, C11.1, C32.1, C33.1, IC3.21, IC3.26, LED1.4, LED2.4, LED3.4, RPI1.2, RPI1.4, RPI1.S2, RPI1.S4, SJ1.1, U3.1, U3.3
AGND: C3.2, C5.2, FB2.1, IC3.28, IC3.33
AVDD: C3.1, C5.1, C16.1, C18.1, C25.1, FB1.1, IC3.32, LEFTMIC0.4, RIGHTMIC0.4
BUTTON: R1.1, RPI1.11, RPI1.S11, SW1.B, SW1.B'
CE0: RPI1.24, RPI1.S24
CE1: RPI1.26, RPI1.S26
EEC: RPI1.28, RPI1.S28
EED: RPI1.27, RPI1.S27
GND: C1.2, C2.2, C7.2, C8.2, C9.2, C10.2, C11.2, C12.2, C13.2, C14.2, C16.2, C18.2, C19.2, C20.2, C21.2, C22.2, C25.2, C26.2, C27.2, C28.2, C29.2, C30.2, C31.2, C32.2, C33.2, C34.2, CONN3.1, D1.A, FB2.2, IC3.9, IC3.20, IC3.24, LED1.3, LED2.3, LED3.3, LEFTMIC0.2, LEFTMIC0.3, NEOPIX0.1, OSC1.2, R4.1, R6.1, RIGHTMIC0.2, RIGHTMIC0.3, RPI1.6, RPI1.9, RPI1.14, RPI1.20, RPI1.25, RPI1.30, RPI1.34, RPI1.39, RPI1.S6, RPI1.S9, RPI1.S14, RPI1.S20, RPI1.S25, RPI1.S30, RPI1.S34, RPI1.S39, SW1.A, SW1.A', SW6.O1, SW6.O2, U3.2, X2.1
GPIO4: RPI1.7, RPI1.S7
GPIO13: RPI1.33, RPI1.S33
GPIO19: RPI1.36, RPI1.S36
GPIO22: RPI1.15, RPI1.S15
GPIO23: RPI1.16, RPI1.S16
GPIO24: RPI1.18, RPI1.S18
GPIO25: RPI1.22, RPI1.S22
GPIO26: RPI1.37, RPI1.S37
GPIO27: RPI1.13, RPI1.S13
I2S_BCLK: IC3.12, RPI1.12, RPI1.S12
I2S_DIN: IC3.16, RPI1.38, RPI1.S38
I2S_DOUT: IC3.14, RPI1.40, RPI1.S40
I2S_LRCLK: IC3.13, IC3.15, RPI1.35, RPI1.S35
LEDC: LED1.2, RPI1.31, RPI1.S31
LEDD: LED1.1, RPI1.29, RPI1.S29
LEFT: C4.-, C27.1, R4.2, X2.2, X2.4
LEFT_N: C31.1, FB10.2, X1.2
LEFT_P: C30.1, FB9.2, X1.1
LINPUT1: C23.2, IC3.4
LSTEMMA: NEOPIX0.3, R7.1
MCLK: IC3.11, OSC1.3
MCLK_EN: OSC1.1, SW6.P1, SW6.P2
MICBIAS: C2.1, C8.1, IC3.1
MISO: RPI1.21, RPI1.S21
MOSI: RPI1.19, RPI1.S19
unnamed: FB7.1, IC3.19
unnamed: FB8.1, IC3.22
unnamed: C6.+, IC3.29
unnamed: C4.+, IC3.31
unnamed: LED1.6, LED2.1
unnamed: LED1.5, LED2.2
unnamed: C19.1, FB3.1, RIGHTMIC0.1
unnamed: C20.1, FB4.1, LEFTMIC0.1
unnamed: LED2.6, LED3.1
unnamed: LED2.5, LED3.2
unnamed: C21.1, C24.1, FB3.2
unnamed: C22.1, C23.1, FB4.2
unnamed: FB9.1, IC3.25
unnamed: FB10.1, IC3.23
OUT: C13.1, C14.1, FB1.2, U3.5
PWM0: D1.C, R7.2, RPI1.32, RPI1.S32
RIGHT: C6.-, C26.1, R6.2, X2.3, X2.5
RIGHT_N: C28.1, FB7.2, X5.2
RIGHT_P: C29.1, FB8.2, X5.1
RINPUT1: C24.2, IC3.5
RXD: RPI1.10, RPI1.S10
SCL: CONN3.4, IC3.17, RPI1.5, RPI1.S5
SCLK: RPI1.23, RPI1.S23
SDA: CONN3.3, IC3.18, RPI1.3, RPI1.S3
TXD: RPI1.8, RPI1.S8
VCC: C34.1, NEOPIX0.2, SJ1.2
VMID: C1.1, C7.1, IC3.27

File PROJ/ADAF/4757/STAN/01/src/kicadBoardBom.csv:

"Id";"Designator";"Package";"Quantity";"Designation";"Supplier and ref";
1;"C3,C25,C14,C12,C16,C7,C8,C18";"0603-NO";8;"0.1uF";;;
2;"C27,C26";"0603-NO";2;"220pF";;;
3;"C21,C20,C19,C22";"0603-NO";4;"33pF";;;
4;"C33";"0805-NO";1;"2.2uF+";;;
5;"C5,C9,C23,C34,C10,C11,C1,C32,C24,C13,C2";"0805-NO";11;"10uF";;;
6;"C30,C29,C31,C28";"0603-NO";4;"100pF";;;
7;"X1,X5";"JSTPH2";2;"JSTPH 2P";;;
8;"U$15";"ADAFRUIT_3.5MM";1;"";;;
9;"X2";"4UCONN_19269";1;"3.5mm";;;
10;"NEOPIX0";"JSTPH3";1;"JST PH 3";;;
11;"R7";"0603-NO";1;"1K";;;
12;"SW6";"EG1390";1;"EG1390";;;
13;"FB9,FB8,FB7,FB10";"0805-NO";4;"120o";;;
14;"U3";"SOT23-5";1;"AP2112-3.3K";;;
15;"OSC1";"OSC_3.2X2.5MM";1;"ECS-3225MV";;;
16;"FB4";"0805-NO";1;"FERRITE";;;
17;"FB2,FB1";"0805";2;"Ferrite";;;
18;"RIGHTMIC0,LEFTMIC0";"SPW2430HR5H-B";2;"";;;
19;"R6";"0603-NO";1;"10k";;;
20;"SW1";"EVQ-Q2_SMALLER";1;"EVQQ";;;
21;"FID2,FID1";"FIDUCIAL_1MM";2;"FIDUCIAL_1MM";;;
22;"C6,C4";"PANASONIC_C";2;"100uF";;;
23;"LED1,LED3,LED2";"APA102";3;"SK6822";;;
24;"FB3";"0805-NO";1;"Ferrite";;;
25;"IC3";"QFN32_5MM";1;"WM8960";;;
26;"R1,R4";"0603-NO";2;"10K";;;
27;"D1";"SOD-323";1;"3.6V";;;
28;"CONN3";"JST_SH4";1;"STEMMA_I2C_QT";;;
29;"RPI1";"PI_BONNET_THMSMT";1;"RASPBERRYPI_BPLUS_BONNET_THMSMT";;;
30;"SJ1";"SOLDERJUMPER_2WAY_OPEN_NOPASTE";1;"";;;
31;"U$12";"STEMMAQT";1;"";;;
32;"U$11";"PCBFEAT-REV-040";1;"";;;
33;"U$16";"ADAFRUIT_TEXT_20MM";1;"";;;
34;"U$79";"BRAINPAD_1IN";1;"";;;

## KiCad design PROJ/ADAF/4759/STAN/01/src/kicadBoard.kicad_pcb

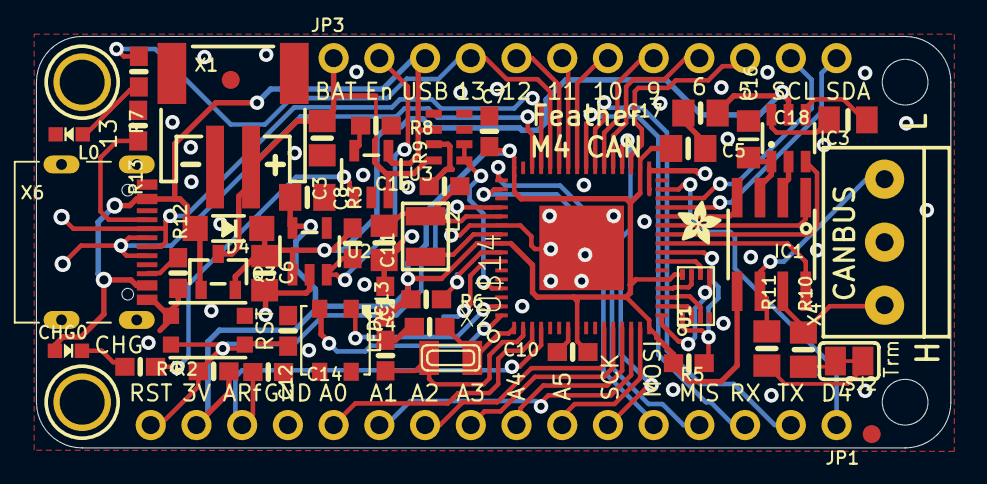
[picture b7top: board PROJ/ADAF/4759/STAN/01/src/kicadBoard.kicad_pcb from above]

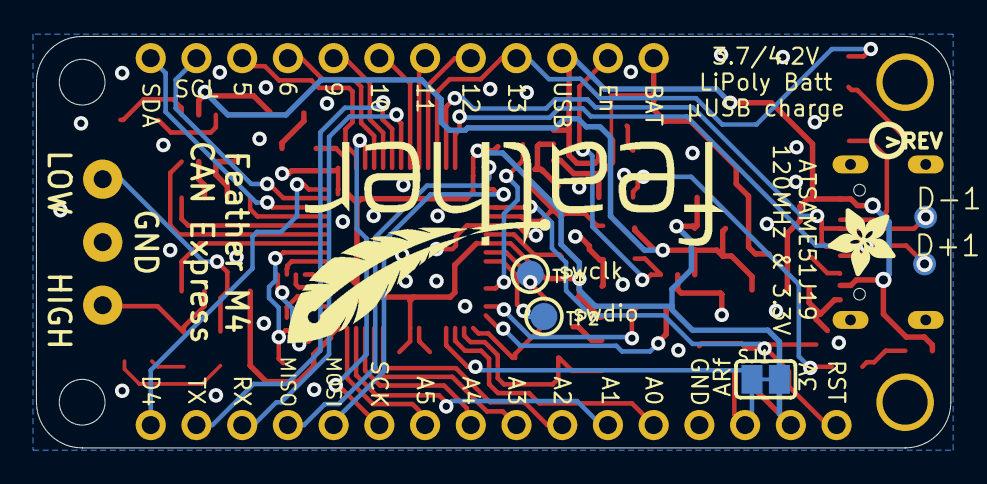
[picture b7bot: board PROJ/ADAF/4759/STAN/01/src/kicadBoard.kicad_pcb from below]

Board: 2 copper layers, 50.8 x 22.9 mm, 63 parts (8 on the bottom side), 63 nets.

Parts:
@HOLE0, @HOLE1: (no value)
C2, C4: 22pF; 0603-NO
C3, C6, C8: 10µF; 0805-NO
C5, C13, C17: 10uF; 0805-NO
C7, C10, C11, C12, C14, C15: 1uF; 0603-NO
C16: 10uF; _0805MP
C18: 1uF; 0805_10MGAP
CHG0: ORANGE; CHIPLED_0603_NOOUTLINE
D4: MBR540; SOD-123
D+1: TPB1,27; B1,27
D-1: TPB1,27; B1,27
IC1: TCAN1051HGV; SOIC8_150MIL
IC3: AP3602; SOT23-6
JP1: 1X16_ROUND
JP3: 1X12_ROUND
L0: RED; CHIPLED_0603_NOOUTLINE
L2: 10uH; INDUCTOR_1007
LED1: WS2812B3535; LED3535
Q3: DMG341; SOT23-R
R2, R3, R4, R5, R6, R7: 10K; 0603-NO
R8, R12, R13: 5.1K; 0603-NO
R9: 100K; RESPACK_4X0603_NO
R10, R11: 60 ohm; 0805-NO
SJ1, SJ2: SOLDERJUMPER_CLOSEDWIRE
SW1: KMR2; BTN_KMR2_4.6X2.8
TP1, TP2: TESTPOINT_ROUND_1.5MM
U1: 2MB Flash; USON8
U2: AP2112-3.3; SOT23-5@1
U3: MCP73831T-2ACI/OT; SOT23-5
U$1: ADAFRUIT_2.5MM
U$9: FEATHERLOGO
U$12: ADAFRUIT_3.5MM
U$13: PCBFEAT-REV-040
U$14: ATSAMD51J; PQFN64-1
U$31, U$32: MOUNTINGHOLE2.5; MOUNTINGHOLE_2.5_PLATED
U$34, U$35: FIDUCIAL_1MM
X1: JSTPH; JSTPH2_BATT
X2: 32.768; XTAL3215
X4: 3.5mm; TERMBLOCK_1X3-3.5MM
X6: USB Type C; USB_C_CUSB31-CFM2AX-01-X

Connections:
5.0V: C16.1, IC1.3, IC3.1
+3V3: C5.1, C7.1, C8.1, C10.1, C11.1, IC1.5, JP1.15, R4.1, R5.2, R6.1, SJ1.2, U1.8, U2.5, U$14.8, U$14.16, U$14.21, U$14.34, U$14.48, U$14.56
A0: JP1.12, U$14.3
A1: JP1.11, U$14.14
A2: JP1.10, U$14.11
A3: JP1.9, U$14.12
A4: JP1.8, U$14.13
A5: JP1.7, U$14.15
AREF: C14.1, JP1.14, SJ1.1, U$14.4
BOOST_EN: IC3.3, U$14.26
CAN1_RX: IC1.4, U$14.28
CAN1_S: IC1.8, U$14.25
CAN1_TX: IC1.1, U$14.27
CAN_H: IC1.7, R10.2, X4.3
CAN_L: IC1.6, R11.2, X4.1
CC1: R13.2, X6.A5
CC2: R12.2, X6.B5
D4: JP1.1, U$14.31
D5: JP3.10, U$14.35
D6: JP3.9, U$14.37
D8_NEOPIX: LED1.1, U$14.63
D9: JP3.8, U$14.38
D10: JP3.7, U$14.41
D11: JP3.6, U$14.42
D12: JP3.5, U$14.43
D13: JP3.4, R7.1, U$14.44
D+: D+1.TP, U$14.46, X6.A6, X6.B6
D-: D-1.TP, U$14.45, X6.A7, X6.B7
EN: JP3.2, R3.1, U2.3
GND: C2.2, C3.2, C4.2, C5.2, C6.2, C7.2, C8.2, C10.2, C11.2, C12.1, C13.2, C14.2, C15.2, C16.2, C17.2, IC1.2, IC3.2, JP1.13, L0.C, LED1.4, R8.2, R9.3, R9.7, R12.1, R13.1, SW1.B, SW1.B', U1.4, U2.2, U3.2, U$14.7, U$14.22, U$14.33, U$14.47, U$14.54, U$14.EXP, X1.1, X4.2, X6.A1B12, X6.B1A12
MISO: JP1.4, U$14.49
MOSI: JP1.5, U$14.50
unnamed: CHG0.C, R2.1
unnamed: L0.A, R7.2
unnamed: R2.2, U3.1
unnamed: R8.1, U3.5
unnamed: R10.1, SJ2.2
unnamed: C4.1, U$14.1, X2.P$2
unnamed: C18.2, IC3.6
unnamed: C18.1, IC3.4
unnamed: C2.1, U$14.2, X2.P$1
unnamed: L2.P$2, U$14.55
unnamed: R11.1, SJ2.1
NEO_PWR: LED1.2, U$14.64
QSPI_CS: R5.1, U1.1, U$14.24
QSPI_DATA[0]: U1.5, U$14.17
QSPI_DATA[1]: U1.2, U$14.18
QSPI_DATA[2]: U1.3, U$14.19
QSPI_DATA[3]: U1.7, U$14.20
QSPI_SCK: U1.6, U$14.23
RX_D0: JP1.3, U$14.40
SCK: JP1.6, U$14.36
SCL: JP3.11, U$14.30
SDA: JP3.12, U$14.29
SWCLK: R6.2, TP1.P$1, U$14.57
SWDIO: TP2.P$1, U$14.58
TX_D1: JP1.2, U$14.39
VBAT: C3.1, JP3.1, Q3.3, R9.8, U3.3, X1.2
VBUS: CHG0.A, D4.A, JP3.3, Q3.1, R9.6, U3.4, X6.A4B9, X6.B4A9
VDDCORE1: C13.1, C15.1, L2.P$1, U$14.53
VHI: C6.1, C17.1, D4.C, IC3.5, Q3.2, R3.2, U2.1
V_DIV: R9.1, R9.2, U$14.61
~RESET: C12.2, JP1.16, R4.2, SW1.A, SW1.A', U$14.52
